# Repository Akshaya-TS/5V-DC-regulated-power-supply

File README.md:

# 5V-DC-regulated-power-supply
Designed a regulated 5V DC power supply using KiCad, including schematic design, footprint assignment, PCB layout, routing, DRC, and Gerber generation. The circuit uses a full-wave rectifier to convert AC to DC, a filter capacitor to reduce ripple, and a 7805 voltage regulator to provide stable 5V DC output for embedded and electronic applications.

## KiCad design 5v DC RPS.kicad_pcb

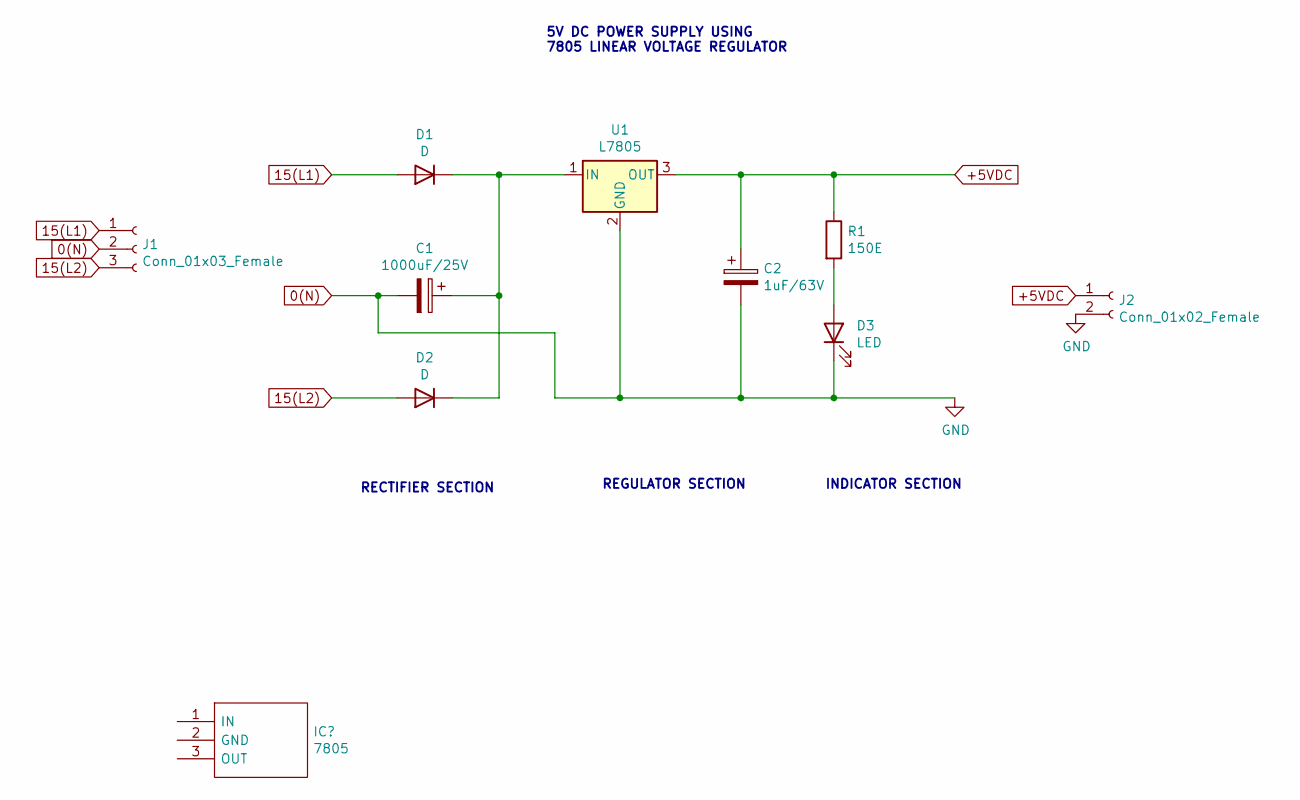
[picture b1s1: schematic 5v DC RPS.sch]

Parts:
C1: 1000uF/25V; CP_Radial_D8.0mm_P3.80mm
C2: 1uF/63V; CP_Radial_D5.0mm_P2.50mm
D1: D; D_DO-27_P15.24mm_Horizontal
D2: D; D_DO-15_P15.24mm_Horizontal
D3: LED; LED_D5.0mm
J1: Conn_01x03_Female; PinHeader_1x03_P2.54mm_Vertical
J2: Conn_01x02_Female; PinHeader_1x02_P2.54mm_Vertical
R1: 150E; R_Axial_DIN0309_L9.0mm_D3.2mm_P12.70mm_Horizontal
U1: L7805; TO-220-3_Vertical

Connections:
0(N): C1.2, C2.2, D3.1 (K), J1.2, J2.2, U1.2 (GND)
15(L1): D1.2 (A), J1.1
15(L2): D2.2 (A), J1.3
+5VDC: C2.1, J2.1, R1.1, U1.3 (OUT)
unnamed: C1.1, D1.1 (K), D2.1 (K), U1.1 (IN)
unnamed: D3.2 (A), R1.2

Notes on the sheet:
5V DC POWER SUPPLY USING 7805 LINEAR VOLTAGE REGULATOR
RECTIFIER SECTION
INDICATOR SECTION
REGULATOR SECTION

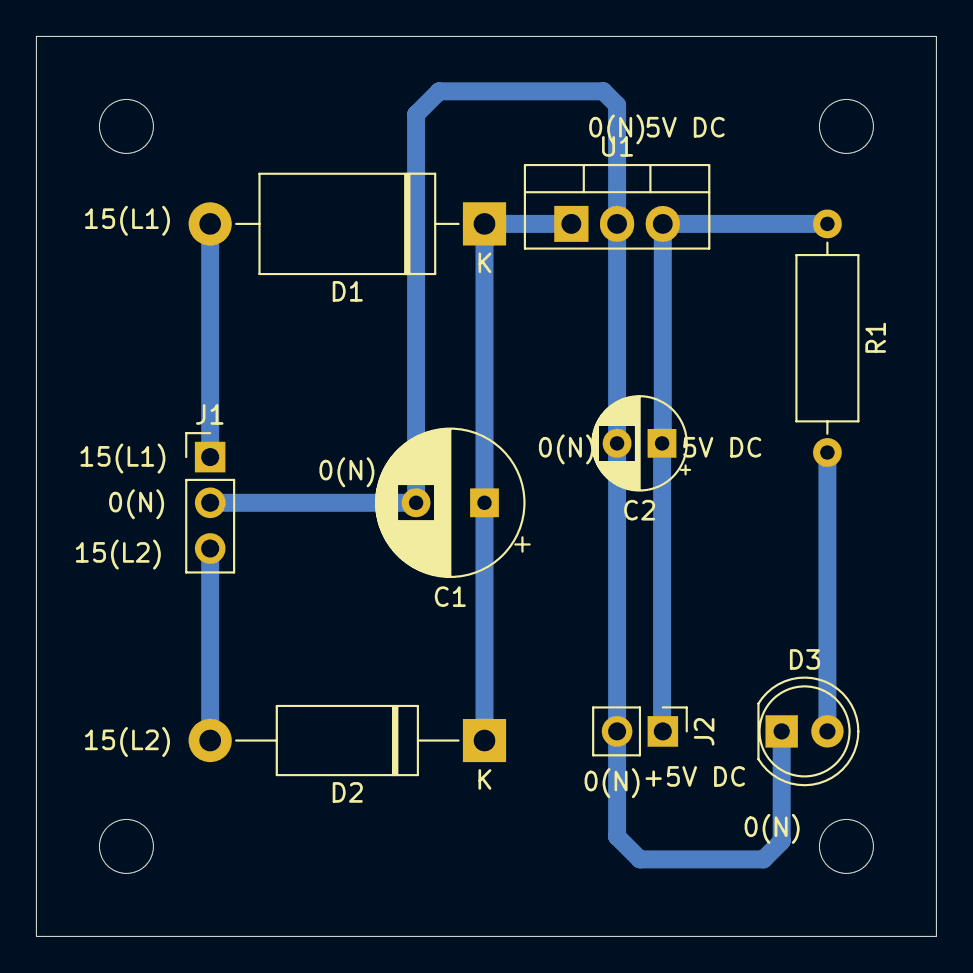
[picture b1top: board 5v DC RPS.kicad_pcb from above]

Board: 2 copper layers, 50.0 x 50.0 mm, 9 parts (0 on the bottom side), 6 nets.

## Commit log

2026-03-03 Add files via upload
    This project involves the design and PCB implementation of a regulated 5V DC power supply using KiCad. The system converts an unregulated DC input (or stepped-down AC) into a stable and constant 5V D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
    The complete design includes:
    1.Schematic capture
    2.PCB layout design
    3.Component placement and routing
    4.Design rule checking (DRC)
